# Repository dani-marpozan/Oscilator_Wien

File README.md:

# Oscilator RC cu retea Wien

Model 3D

## Schematic

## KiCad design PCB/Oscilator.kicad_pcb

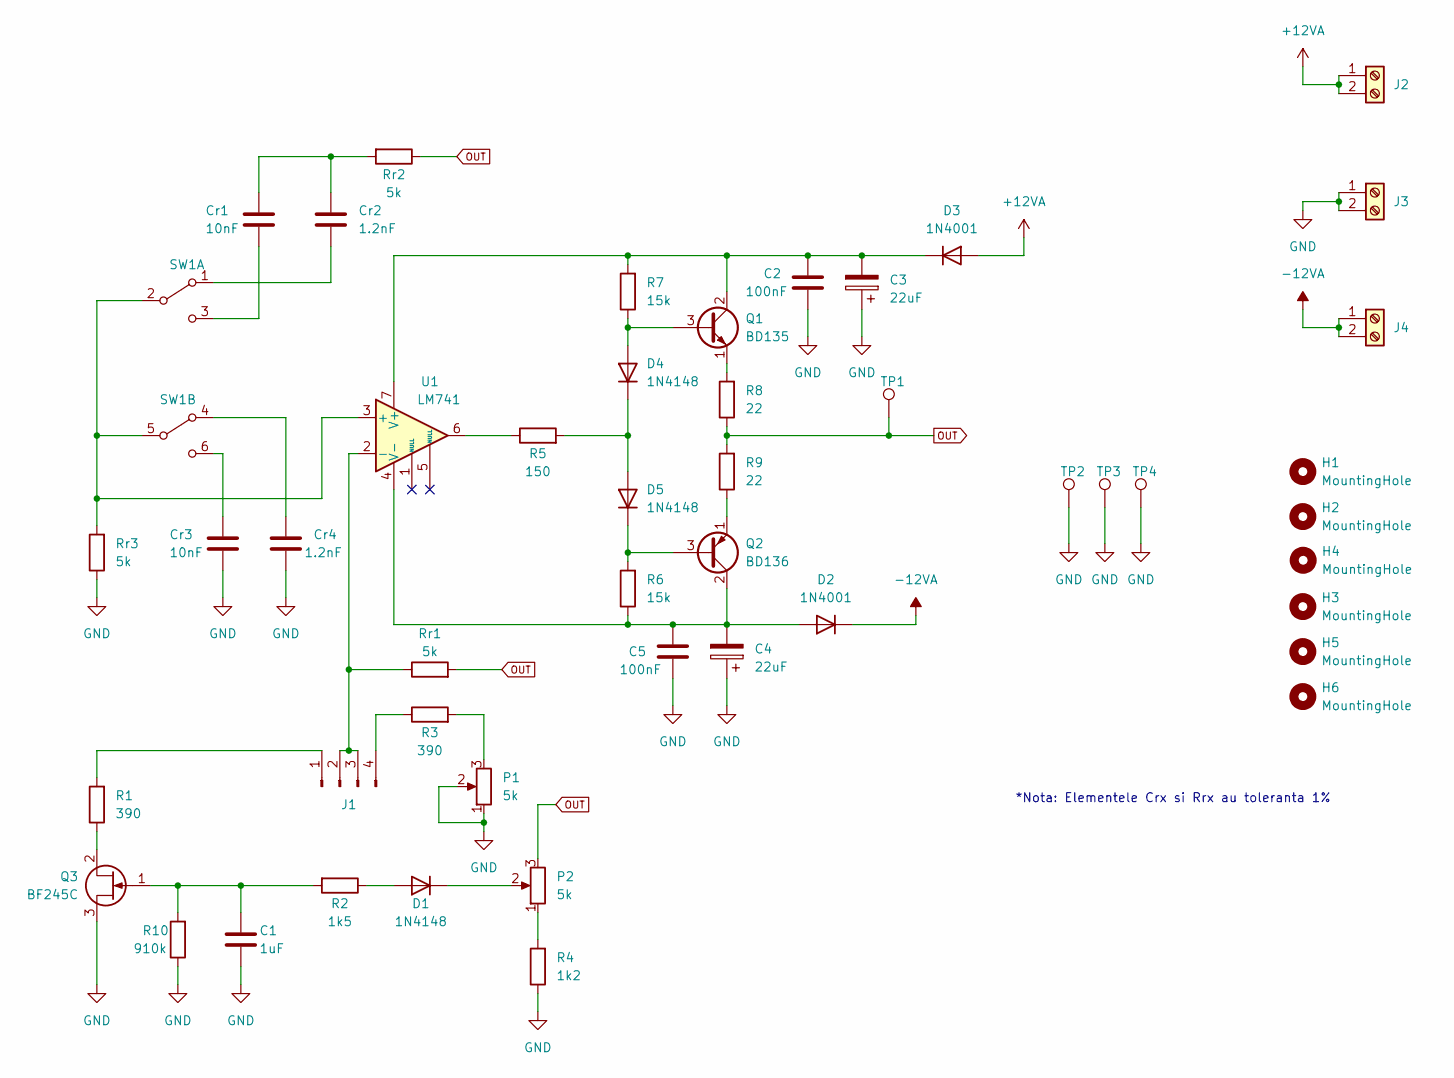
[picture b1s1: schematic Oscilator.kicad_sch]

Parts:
C1: 1uF; C_Radial_D5.0mm_H11.0mm_P2.00mm
C2, C5: 100nF; C_Disc_D6.0mm_W2.5mm_P5.00mm
C3, C4: 22uF; C_Radial_D5.0mm_H11.0mm_P2.00mm
Cr1, Cr3: 10nF; C_Axial_L12.0mm_D8.5mm_P20.00mm_Horizontal
Cr2, Cr4: 1.2nF; C_Axial_L5.1mm_D3.1mm_P12.50mm_Horizontal
D1, D4, D5: 1N4148; D_DO-35_SOD27_P7.62mm_Horizontal
D2, D3: 1N4001; D_DO-41_SOD81_P10.16mm_Horizontal
H1, H2, H3, H4: MountingHole; MountingHole_3.2mm_M3_ISO7380_Pad_TopBottom
H5, H6: MountingHole; MountingHole_3.2mm_M3
J1: Conn_01x04_Male; PinHeader_1x04_P2.54mm_Vertical
J2, J3, J4: Screw_Terminal_01x02; TerminalBlock_Phoenix_MKDS-1,5-2_1x02_P5.00mm_Horizontal
P1, P2: 5k; Custom Potentiometer footprint
Q1: BD135; TO-126-3_Vertical
Q2: BD136; TO-126-3_Vertical
Q3: BF245C; TO-92_Inline
R1, R3: 390; R_Axial_DIN0207_L6.3mm_D2.5mm_P10.16mm_Horizontal
R2: 1k5; R_Axial_DIN0207_L6.3mm_D2.5mm_P10.16mm_Horizontal
R4: 1k2; R_Axial_DIN0207_L6.3mm_D2.5mm_P10.16mm_Horizontal
R5: 150; R_Axial_DIN0207_L6.3mm_D2.5mm_P10.16mm_Horizontal
R6, R7: 15k; R_Axial_DIN0207_L6.3mm_D2.5mm_P10.16mm_Horizontal
R8, R9: 22; R_Axial_DIN0516_L15.5mm_D5.0mm_P20.32mm_Horizontal
R10: 910k; R_Axial_DIN0207_L6.3mm_D2.5mm_P10.16mm_Horizontal
Rr1, Rr2, Rr3: 5k; R_Axial_DIN0207_L6.3mm_D2.5mm_P10.16mm_Horizontal
SW1: SW_DPDT_x2; OS202013MT8QN1
TP1: TestPoint; Kesytone TP Multipurpose 5013
TP2, TP3, TP4: TestPoint
U1: LM741; DIP-8_W7.62mm

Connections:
+12VA: D3.2 (A), J2.1, J2.2
-12VA: D2.1 (K), J4.1, J4.2
GND: C1.2, C2.2, C3.1, C4.1, C5.2, Cr3.2, Cr4.2, J3.1, J3.2, P1.1, P1.2, Q3.3 (D), R4.1, R10.1, Rr3.1, TP2.1, TP3.1, TP4.1
unnamed: Cr1.1, Cr2.1, Rr2.2
unnamed: D1.2 (A), R2.1
unnamed: D1.1 (K), P2.2
unnamed: C4.2, C5.1, D2.2 (A), Q2.2 (C), R6.1, U1.4 (V-)
unnamed: C2.1, C3.2, D3.1 (K), Q1.2 (C), R7.2, U1.7 (V+)
unnamed: D4.2 (A), Q1.3 (B), R7.1
unnamed: D4.1 (K), D5.2 (A), R5.2
unnamed: D5.1 (K), Q2.3 (B), R6.2
unnamed: J1.1, R1.2
unnamed: J1.2, J1.3, Rr1.1, U1.2 (-)
unnamed: J1.4, R3.1
unnamed: P1.3, R3.2
unnamed: P2.1, R4.2
unnamed: Q1.1 (E), R8.2
unnamed: Q2.1 (E), R9.1
unnamed: C1.1, Q3.1 (G), R2.2, R10.2
unnamed: Q3.2 (S), R1.1
unnamed: R5.1, U1.6
unnamed: Cr2.2, SW1.1 (A)
unnamed: Rr3.2, SW1.2 (B), SW1.5 (B), U1.3 (+)
unnamed: Cr1.2, SW1.3 (C)
unnamed: Cr4.1, SW1.4 (A)
unnamed: Cr3.1, SW1.6 (C)
OUT: P2.3, R8.1, R9.2, Rr1.2, Rr2.1, TP1.1

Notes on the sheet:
*Nota: Elementele Crx si Rrx au toleranta 1%

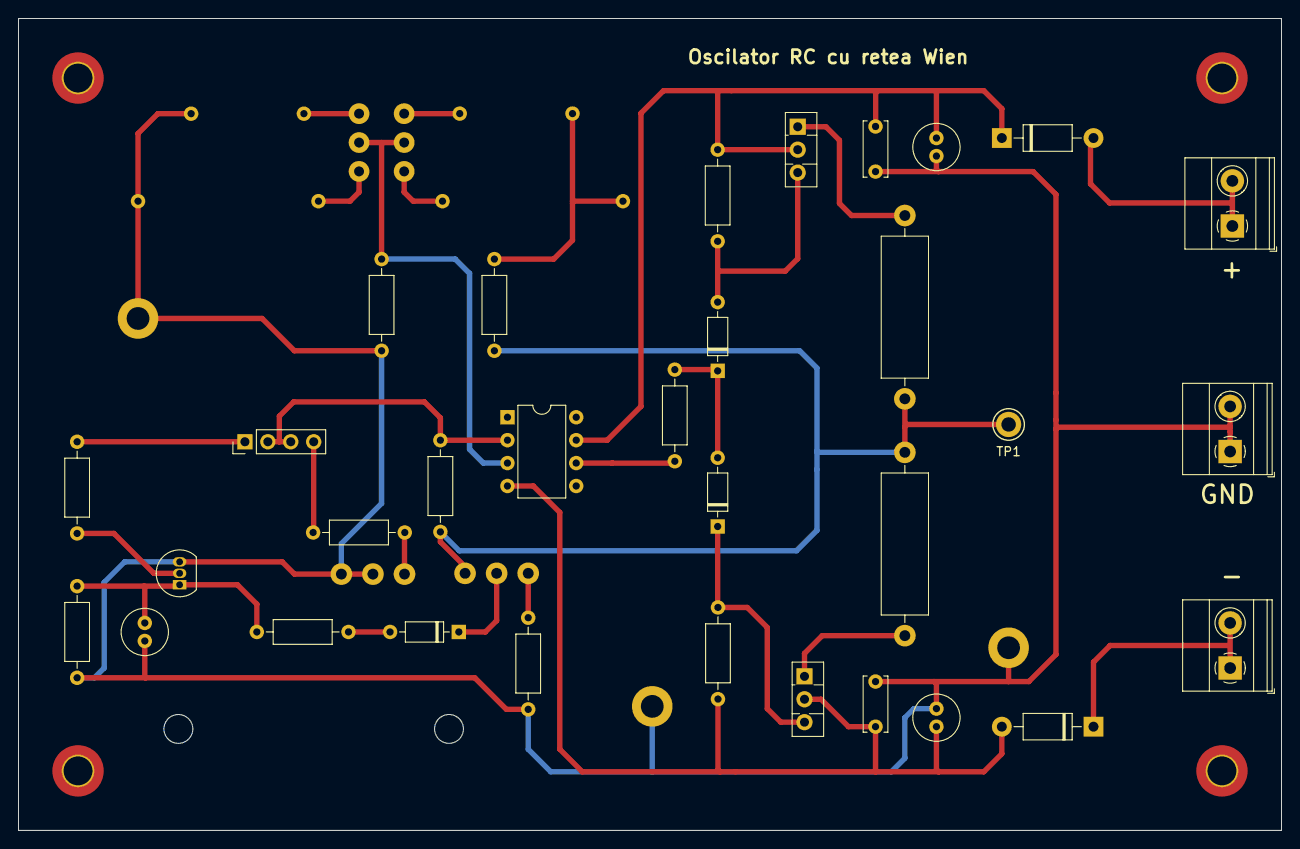
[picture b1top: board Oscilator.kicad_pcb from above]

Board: 2 copper layers, 140.0 x 90.0 mm, 48 parts (0 on the bottom side), 27 nets.
